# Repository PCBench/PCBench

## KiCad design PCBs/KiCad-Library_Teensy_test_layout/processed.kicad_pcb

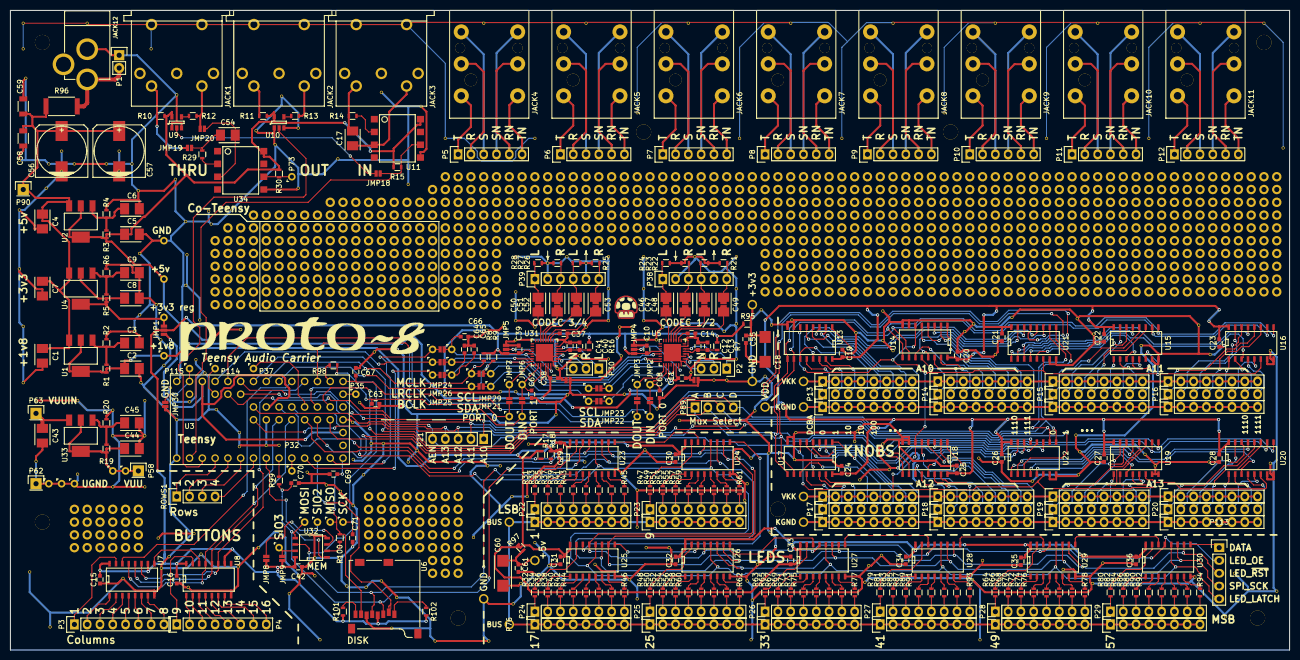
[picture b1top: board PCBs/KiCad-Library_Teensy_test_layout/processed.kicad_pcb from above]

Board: 2 copper layers, 254.0 x 127.0 mm, 372 parts (0 on the bottom side), 408 nets.

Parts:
C1, C2, C3, C4, C5, C6, C7, C8, C9, C43, C44, C45: 10u; TantalC_SizeB_EIA-3528_Reflow
C10, C11, C12, C13, C14, C37, C38, C39, C40, C41: 0.1uF; C_0603
C15, C16, C29, C30, C31, C32, C33, C34, C35, C36, C42: C; C_0603
C17, C54: D; TantalC_SizeB_EIA-3528_Reflow
C18, C60: 68uF; TantalC_SizeC_EIA-6032_Reflow
C19, C20, C21, C22, C23, C24, C25, C26, C27, C28: 1u; C_0603
C46, C47, C48, C49, C50, C51, C52, C53: 2.2u; TantalC_SizeB_EIA-3528_Reflow
C55, C61: 1uF; C_0603
C56, C57: 100u; c_elec_10x10.5
C58, C59: 1u; C_1206
C62, C63, C64, C65, C66, C67, C68, C69, C70, C71: 22p; C_0603
H1, H2, H3, H4, H5, H6, H7, H8: Hole; MountingHole_3mm
JACK1, JACK2, JACK3: DIN-5; SF-DIN-5
JACK4, JACK5, JACK6, JACK7, JACK8, JACK9, JACK10, JACK11: TRS_6term; SF-Neutrik-Jack-6-term
JACK12: POWER_JACKPTH; SparkFun-Connectors-POWER_JACK_PTH
JMP1, JMP4, JMP5: 3Jumper; SF-3way-open
JMP2, JMP3, JMP6, JMP7, JMP8, JMP9, JMP10, JMP11, JMP12, JMP13, JMP14, JMP15, JMP16, JMP17, JMP21, JMP22, JMP23, JMP24, JMP25, JMP26, JMP27, JMP28, JMP29, JMP30: 2Jumper; SF-2way-open
JMP18: THRU; SF-2way-open
JMP19, JMP20: IN2; SF-2way-open
P1: CONN_01X02; Pin_Header_Straight_1x02
P2, P30: CONN_01X03; Pin_Header_Straight_1x03
P3: COLS0; Pin_Header_Straight_1x08
P4: COLS1; Pin_Header_Straight_1x08
P5, P6, P7, P8, P9, P10, P11, P12, P38, P39: CONN_01X06; Pin_Header_Straight_1x06
P13, P14, P15, P16, P17, P18, P19, P20, P22, P23, P24, P25, P26, P27, P28, P29, P40, P41, P42, P43, P44, P45, P46, P47, P48, P49, P50, P51, P52, P53, P54, P55, P74, P75, P76, P77, P78, P79, P80, P81: CONN_01X08; Pin_Header_Straight_1x08
P21, P113: CONN_01X05; Pin_Header_Straight_1x05
P31, P36, P56, P57, P59, P60, P61, P104, P105, P114, P115: CONN_01X01; TestHole
P32: PIN8; TestHole
P33: SIO2; TestHole
P34: ~HOLD~/SIO3; TestHole
P35: PIN37; TestHole
P37: PIN31; TestHole
P58: VUU; Pin_Header_Straight_1x01
P62: UGND; Pin_Header_Straight_1x01
P63, P90: CONN_01X01; Pin_Header_Straight_1x01
P64: DIN1; TestHole
P65: DOUT1; TestHole
P66: SDA0_ISO; TestHole
P67: SCL0_ISO; TestHole
P68: MCLK_ISO; TestHole
P69: BCLK_ISO; TestHole
P70: LRCLK_ISO; TestHole
P71: DIN0; TestHole
P72: DOUT0; TestHole
P73: IN2TTL; TestHole
P82, P83, P84, P85, P86, P87, P88, P103, P106, P107, P108: CONN_01X01; PTH_LUG_.05
P89: CONN_01X04; Pin_Header_Straight_1x04
P91: SDA0; TestHole
P92: SCL0; TestHole
P93: MCLK; TestHole
P94: BCLK; TestHole
P95: LRCLK; TestHole
P96: DIN1_ISO; TestHole
P97: DOUT1_ISO; TestHole
P98: DIN0_ISO; TestHole
P99: DOUT0_ISO; TestHole
P100: SPI_MOSI; TestHole
P101: SPI_MISO; TestHole
P102: SPI_SCK; TestHole
P109: SCL_ISO; TestHole
P110: SDA_ISO; TestHole
P111: SCL_ISO2; TestHole
P112: SDA_ISO2; TestHole
R1, R3, R19: 11.3K; R_0603
R2, R4, R20: 34K; R_0603
R5: 11.5K; R_0603
R6: 18.7K; R_0603
R7, R16, R95, R97: 1; R_0603
R8, R9: 2.2K; R_0603
R10, R11, R12, R13, R14, R15, R29, R30: 220; R_0603
R17, R18, R101, R102: 4.7k; R_0603
R21, R22, R23, R24, R25, R26, R27, R28: 100k; R_0603
R31, R32, R33, R34, R35, R36, R37, R38, R39, R40, R41, R42, R43, R44, R45, R46, R47, R48, R49, R50, R51, R52, R53, R54, R55, R56, R57, R58, R59, R60, R61, R62, R63, R64, R65, R66, R67, R68, R69, R70, R71, R72, R73, R74, R75, R76, R77, R78, R79, R80, R81, R82, R83, R84, R85, R86, R87, R88, R89, R90, R91, R92, R93, R94: 470; R_0603
R96: 1; R_2512
R98, R99, R100: 50; R_0603
ROWS1: CONN_01X04; Pin_Header_Straight_1x04
U1, U2, U4, U33: LDO-adj-4term; SF-SOT-223
U3: Teensy_3.2; Teensy_3.2_Grid
U5, U31: SGTL5000; SF-QFN-32-NXP-SGTL5000
U6: SF-MicroSD-12term; SF-MICRO-SD
U7, U8, U23, U24, U25, U26, U27, U28, U29, U30: SF-74HC595; SF-SOIC-16
U9, U10: SF-74x125; SF-SOT-23-5
U11, U34: 2N168; SF-SMD-8
U13, U14, U15, U16, U17, U18, U19, U20, U21, U22: SF-4052; SF-SOIC-16
U32: SPI_MEMORY_SOIC8; SF-SOIC-8

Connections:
1/2AINL: C46.2, JMP13.1, U5.14
1/2AINR: C47.2, JMP12.1, U5.13
1/2AOUTL: C48.2, JMP11.1, U5.12
1/2AOUTR: C49.2, JMP10.1, U5.11
3/4AINL: C50.2, JMP17.1, U31.14
3/4AINR: C51.2, JMP16.1, U31.13
3/4AOUTL: C52.2, JMP15.1, U31.12
3/4AOUTR: C53.2, JMP14.1, U31.11
!LED_RST: P113.3, R18.1, U3.26, U23.10, U24.10, U25.10, U26.10, U27.10, U28.10, U29.10, U30.10
+1V8: C2.1, C11.1, C38.1, P104.1, R1.1, U1.2, U1.4, U5.30, U31.30
+3V3: C10.1, C15.1, C16.1, C39.1, C42.1, JMP1.2, JMP4.3, JMP5.3, JMP8.1, JMP9.1, R7.1, R8.1, R9.1, R16.1, R95.2, R101.1, R102.1, U5.20, U6.4, U7.10, U7.16, U8.10, U8.16, U31.20, U32.8
+3V3_REG: C8.1, JMP1.3, P105.1, R5.1, U4.2, U4.4
+3V3_TOUT: JMP1.1, U3.36, U3.40, U3.43
+5V: C5.1, C29.1, C30.1, C31.1, C32.1, C33.1, C34.1, C35.1, C36.1, P31.1, R3.1, R10.1, R11.1, R15.1, R17.1, R30.1, R97.2, U2.2, U2.4, U3.34, U9.5, U10.5, U11.8, U23.16, U24.16, U25.16, U26.16, U27.16, U28.16, U29.16, U30.16, U34.8
A: P89.1, U3.27, U13.10, U14.10, U15.10, U16.10, U17.10, U18.10, U19.10, U20.10
AGND: JMP30.2, P115.1, U3.35
AREF: P114.1, U3.48
B: P89.2, U3.28, U13.9, U14.9, U15.9, U16.9, U17.9, U18.9, U19.9, U20.9
BCLK: U3.16, U7.11, U8.11
BCLK_ISO: C65.1, JMP25.2, P69.1, U5.24, U31.24
BLATCH: U3.24, U7.12, U8.12
BOE: U3.25, U7.13, U8.13
BSER: U3.17, U7.14
C: P89.3, U3.29, U21.10, U22.10
CHASSIS: JACK1.6, JACK1.7, JACK2.6, JACK2.7, JACK3.6, JACK3.7
D: P89.4, U3.20, U21.9, U22.9
EN: P21.5, U3.21, U13.6, U14.6, U15.6, U16.6, U17.6, U18.6, U19.6, U20.6, U21.6, U22.6
GND: C1.2, C2.2, C3.2, C4.2, C5.2, C6.2, C7.2, C8.2, C9.2, C15.2, C16.2, C18.2, C19.2, C20.2, C21.2, C22.2, C23.2, C24.2, C25.2, C26.2, C27.2, C28.2, C29.2, C30.2, C31.2, C32.2, C33.2, C34.2, C35.2, C36.2, C42.2, C55.2, C56.2, C57.2, C58.2, C59.2, C60.2, C61.2, C62.2, C63.2, C64.2, C65.2, C66.2, C67.2, C68.2, C69.2, C70.2, C71.2, JACK12.GND, JMP27.1, JMP28.1, JMP30.1, P1.1, P36.1, P84.1, P107.1, R2.2, R4.2, R6.2, R18.2, U3.39, U3.42, U3.50, U6.6, U7.8, U8.8, U9.1, U9.3, U10.1, U10.3, U11.5, U13.7, U13.8, U14.7, U14.8, U15.7, U15.8, U16.7, U16.8, U17.7, U17.8, U18.7, U18.8, U19.7, U19.8, U20.7, U20.8, U21.7, U21.8, U22.7, U22.8, U23.8, U24.8, U25.8, U26.8, U27.8, U28.8, U29.8, U30.8, U32.4, U34.5
I2S_BCLK: JMP25.1, P94.1, U3.9
I2S_DIN0: JMP2.1, P71.1, U3.22
I2S_DIN0_ISO: C68.1, JMP2.2, P98.1, U5.26
I2S_DIN1: JMP6.1, P64.1, U3.15
I2S_DIN1_ISO: C62.1, JMP6.2, P96.1, U31.26
I2S_DOUT0: C67.1, JMP3.1, P72.1, U3.13
I2S_DOUT0_ISO: JMP3.2, P99.1, U5.25
I2S_DOUT1: C63.1, JMP7.1, P65.1, U3.30
I2S_DOUT1_ISO: JMP7.2, P97.1, U31.25
I2S_LRCLK: JMP26.1, P95.1, U3.23
I2S_MCLK: JMP24.1, P93.1, U3.11
ISOGND12: C10.2, C11.2, C12.2, C13.2, C14.2, JMP4.1, JMP27.2, P38.2, P38.5, R21.2, R22.2, R23.2, R24.2, U5.1, U5.3, U5.7, U5.32, U5.33
ISOGND34: C37.2, C38.2, C39.2, C40.2, C41.2, JMP5.1, JMP28.2, P39.2, P39.5, R25.2, R26.2, R27.2, R28.2, U31.1, U31.3, U31.7, U31.32, U31.33
K1: P13.1, U13.12
K2: P13.2, U13.14
K3: P13.3, U13.15
K4: P13.4, U13.11
K5: P13.5, U13.1
K6: P13.6, U13.5
K7: P13.7, U13.2
K8: P13.8, U13.4
K9: P14.1, U14.12
K10: P14.2, U14.14
K11: P14.3, U14.15
K12: P14.4, U14.11
K13: P14.5, U14.1
K14: P14.6, U14.5
K15: P14.7, U14.2
K16: P14.8, U14.4
K17: P15.1, U15.12
K18: P15.2, U15.14
K19: P15.3, U15.15
K20: P15.4, U15.11
K21: P15.5, U15.1
K22: P15.6, U15.5
K23: P15.7, U15.2
K24: P15.8, U15.4
K25: P16.1, U16.12
K26: P16.2, U16.14
K27: P16.3, U16.15
K28: P16.4, U16.11
K29: P16.5, U16.1
K30: P16.6, U16.5
K31: P16.7, U16.2
K32: P16.8, U16.4
K33: P17.1, U17.12
K34: P17.2, U17.14
K35: P17.3, U17.15
K36: P17.4, U17.11
K37: P17.5, U17.1
K38: P17.6, U17.5
K39: P17.7, U17.2
K40: P17.8, U17.4
K41: P18.1, U18.12
K42: P18.2, U18.14
K43: P18.3, U18.15
K44: P18.4, U18.11
K45: P18.5, U18.1
K46: P18.6, U18.5
K47: P18.7, U18.2
K48: P18.8, U18.4
K49: P19.1, U19.12
K50: P19.2, U19.14
K51: P19.3, U19.15
K52: P19.4, U19.11
K53: P19.5, U19.1
K54: P19.6, U19.5
K55: P19.7, U19.2
K56: P19.8, U19.4
K57: P20.1, U20.12
K58: P20.2, U20.14
K59: P20.3, U20.15
K60: P20.4, U20.11
K61: P20.5, U20.1
K62: P20.6, U20.5
K63: P20.7, U20.2
K64: P20.8, U20.4
KA0: P21.1, U3.44, U21.13
KA1: P21.2, U3.45, U21.3
KA2: P21.3, U3.46, U22.13
KA3: P21.4, U3.47, U22.3
KGND: P48.1, P48.2, P48.3, P48.4, P48.5, P48.6, P48.7, P48.8, P49.1, P49.2, P49.3, P49.4, P49.5, P49.6, P49.7, P49.8, P50.1, P50.2, P50.3, P50.4, P50.5, P50.6, P50.7, P50.8, P51.1, P51.2, P51.3, P51.4, P51.5, P51.6, P51.7, P51.8, P85.1
KGND2: P52.1, P52.2, P52.3, P52.4, P52.5, P52.6, P52.7, P52.8, P53.1, P53.2, P53.3, P53.4, P53.5, P53.6, P53.7, P53.8, P54.1, P54.2, P54.3, P54.4, P54.5, P54.6, P54.7, P54.8, P55.1, P55.2, P55.3, P55.4, P55.5, P55.6, P55.7, P55.8, P86.1
KOUT1: U13.13, U21.12
KOUT2: U13.3, U21.14
KOUT3: U14.13, U21.15
KOUT4: U14.3, U21.11
KOUT5: U15.13, U21.1
KOUT6: U15.3, U21.5
KOUT7: U16.13, U21.2
KOUT8: U16.3, U21.4
KOUT9: U17.13, U22.12
KOUT10: U17.3, U22.14
KOUT11: U18.13, U22.15
KOUT12: U18.3, U22.11
KOUT13: U19.13, U22.1
KOUT14: U19.3, U22.5
KOUT15: U20.13, U22.2
KOUT16: U20.3, U22.4
LED_BUS: P74.1, P74.2, P74.3, P74.4, P74.5, P74.6, P74.7, P74.8, P75.1, P75.2, P75.3, P75.4, P75.5, P75.6, P75.7, P75.8, P76.1, P76.2, P76.3, P76.4, P76.5, P76.6, P76.7, P76.8, P77.1, P77.2, P77.3, P77.4, P77.5, P77.6, P77.7, P77.8, P78.1, P78.2, P78.3, P78.4, P78.5, P78.6, P78.7, P78.8, P79.1, P79.2, P79.3, P79.4, P79.5, P79.6, P79.7, P79.8, P80.1, P80.2, P80.3, P80.4, P80.5, P80.6, P80.7, P80.8, P81.1, P81.2, P81.3, P81.4, P81.5, P81.6, P81.7, P81.8, P87.1, P88.1
LED_LATCH: P113.5, U3.32, U23.12, U24.12, U25.12, U26.12, U27.12, U28.12, U29.12, U30.12
LED_OE: P113.2, R17.2, U3.33, U23.13, U24.13, U25.13, U26.13, U27.13, U28.13, U29.13, U30.13
LRCLK_ISO: C64.1, JMP26.2, P70.1, U5.23, U31.23
MCLK_ISO: C66.1, JMP24.2, P68.1, U5.21, U31.21
unnamed: C3.1, R1.2, R2.1, U1.1
unnamed: C6.1, R3.2, R4.1, U2.1
unnamed: C9.1, R5.2, R6.1, U4.1
unnamed: C12.1, C13.1, R7.2, U5.5
unnamed: C14.1, U5.10
unnamed: C17.1, JACK3.5, U11.3
unnamed: C17.2, JACK3.4, R14.1
unnamed: C18.1, C55.1, P103.1, R95.1
unnamed: C37.1, U31.10
unnamed: C40.1, C41.1, R16.2, U31.5
unnamed: C45.1, R19.2, R20.1, U33.1
unnamed: C46.1, JMP13.2, P38.1, R24.1
unnamed: C47.1, JMP12.2, P38.3, R23.1
unnamed: C48.1, JMP11.2, P38.4, R22.1
unnamed: C49.1, JMP10.2, P38.6, R21.1
unnamed: C50.1, JMP17.2, P39.1, R28.1
unnamed: C51.1, JMP16.2, P39.3, R27.1
unnamed: C52.1, JMP15.2, P39.4, R26.1
unnamed: C53.1, JMP14.2, P39.6, R25.1
unnamed: C54.1, JMP20.1, U34.3
unnamed: C54.2, JMP19.1, R29.2
unnamed: C60.1, C61.1, P106.1, R97.1
unnamed: JACK1.4, JMP19.2, R10.2
unnamed: JACK1.5, JMP20.2, R12.1
unnamed: JACK2.4, R11.2
unnamed: JACK2.5, R13.1
unnamed: JACK4.G, P5.4
unnamed: JACK4.R, P5.2
unnamed: JACK4.RN, P5.5
unnamed: JACK4.S, P5.3
unnamed: JACK4.T, P5.1
unnamed: JACK4.TN, P5.6
unnamed: JACK5.G, P6.4
unnamed: JACK5.R, P6.2
unnamed: JACK5.RN, P6.5
unnamed: JACK5.S, P6.3
unnamed: JACK5.T, P6.1
unnamed: JACK5.TN, P6.6
unnamed: JACK6.G, P7.4
unnamed: JACK6.R, P7.2
unnamed: JACK6.RN, P7.5
unnamed: JACK6.S, P7.3
unnamed: JACK6.T, P7.1
unnamed: JACK6.TN, P7.6
unnamed: JACK7.G, P8.4
unnamed: JACK7.R, P8.2
unnamed: JACK7.RN, P8.5
unnamed: JACK7.S, P8.3
unnamed: JACK7.T, P8.1
unnamed: JACK7.TN, P8.6
unnamed: JACK8.G, P9.4
unnamed: JACK8.R, P9.2
unnamed: JACK8.RN, P9.5
unnamed: JACK8.S, P9.3
unnamed: JACK8.T, P9.1
unnamed: JACK8.TN, P9.6
unnamed: JACK9.G, P10.4
unnamed: JACK9.R, P10.2
unnamed: JACK9.RN, P10.5
unnamed: JACK9.S, P10.3
unnamed: JACK9.T, P10.1
unnamed: JACK9.TN, P10.6
unnamed: JACK10.G, P11.4
unnamed: JACK10.R, P11.2
unnamed: JACK10.RN, P11.5
unnamed: JACK10.S, P11.3
unnamed: JACK10.T, P11.1
unnamed: JACK10.TN, P11.6
unnamed: JACK11.G, P12.4
unnamed: JACK11.R, P12.2
unnamed: JACK11.RN, P12.5
unnamed: JACK11.S, P12.3
unnamed: JACK11.T, P12.1
unnamed: JACK11.TN, P12.6
unnamed: JMP4.2, U5.31
unnamed: JMP5.2, U31.31
unnamed: JMP8.2, P33.1, U32.3
unnamed: JMP9.2, P34.1, U32.7
unnamed: JMP18.2, U9.2
unnamed: P2.1, U5.6
unnamed: P2.2, U5.2
unnamed: P2.3, U5.4
unnamed: P3.1, U7.15
unnamed: P3.2, U7.1
unnamed: P3.3, U7.2
unnamed: P3.4, U7.3
unnamed: P3.5, U7.4
unnamed: P3.6, U7.5
unnamed: P3.7, U7.6
unnamed: P3.8, U7.7
unnamed: P4.1, U8.15
unnamed: P4.2, U8.1
unnamed: P4.3, U8.2
unnamed: P4.4, U8.3
unnamed: P4.5, U8.4
unnamed: P4.6, U8.5
unnamed: P4.7, U8.6
unnamed: P4.8, U8.7
unnamed: P22.1, R31.1
unnamed: P22.2, R33.1
unnamed: P22.3, R35.1
unnamed: P22.4, R37.1
unnamed: P22.5, R39.1
unnamed: P22.6, R41.1
unnamed: P22.7, R43.1
unnamed: P22.8, R45.1
unnamed: P23.1, R47.1
unnamed: P23.2, R49.1
unnamed: P23.3, R51.1
unnamed: P23.4, R53.1
unnamed: P23.5, R55.1
unnamed: P23.6, R57.1
unnamed: P23.7, R59.1
unnamed: P23.8, R61.1
unnamed: P24.1, R32.1
unnamed: P24.2, R34.1
unnamed: P24.3, R36.1
unnamed: P24.4, R38.1
unnamed: P24.5, R40.1
unnamed: P24.6, R42.1
unnamed: P24.7, R44.1
unnamed: P24.8, R46.1
unnamed: P25.1, R48.1
unnamed: P25.2, R50.1
unnamed: P25.3, R52.1
unnamed: P25.4, R54.1
unnamed: P25.5, R56.1
unnamed: P25.6, R58.1
unnamed: P25.7, R60.1
unnamed: P25.8, R62.1
unnamed: P26.1, R63.1
unnamed: P26.2, R65.1
unnamed: P26.3, R67.1
unnamed: P26.4, R69.1
unnamed: P26.5, R71.1
unnamed: P26.6, R73.1
unnamed: P26.7, R75.1
unnamed: P26.8, R77.1
unnamed: P27.1, R79.1
unnamed: P27.2, R81.1
unnamed: P27.3, R83.1
unnamed: P27.4, R85.1
unnamed: P27.5, R87.1
unnamed: P27.6, R89.1
unnamed: P27.7, R91.1
unnamed: P27.8, R93.1
unnamed: P28.1, R64.1
unnamed: P28.2, R66.1
unnamed: P28.3, R68.1
unnamed: P28.4, R70.1
unnamed: P28.5, R72.1
unnamed: P28.6, R74.1
unnamed: P28.7, R76.1
unnamed: P28.8, R78.1
unnamed: P29.1, R80.1
unnamed: P29.2, R82.1
unnamed: P29.3, R84.1
unnamed: P29.4, R86.1
unnamed: P29.5, R88.1
unnamed: P29.6, R90.1
unnamed: P29.7, R92.1
unnamed: P29.8, R94.1
unnamed: P30.1, U31.6
unnamed: P30.2, U31.2
unnamed: P30.3, U31.4
unnamed: P32.1, U3.8
unnamed: P35.1, U3.37
unnamed: P37.1, U3.31
unnamed: P73.1, R30.2, U34.6
unnamed: P113.1, U30.9
unnamed: R12.2, U9.4
unnamed: R13.2, U10.4
unnamed: R14.2, U11.2
unnamed: R29.1, U34.2
unnamed: R31.2, U23.15
unnamed: R32.2, U25.15
unnamed: R33.2, U23.1
unnamed: R34.2, U25.1
unnamed: R35.2, U23.2
unnamed: R36.2, U25.2
unnamed: R37.2, U23.3
unnamed: R38.2, U25.3
unnamed: R39.2, U23.4
unnamed: R40.2, U25.4
unnamed: R41.2, U23.5
unnamed: R42.2, U25.5
unnamed: R43.2, U23.6
unnamed: R44.2, U25.6
unnamed: R45.2, U23.7
unnamed: R46.2, U25.7
unnamed: R47.2, U24.15
unnamed: R48.2, U26.15
unnamed: R49.2, U24.1
unnamed: R50.2, U26.1
unnamed: R51.2, U24.2
unnamed: R52.2, U26.2
unnamed: R53.2, U24.3
unnamed: R54.2, U26.3
unnamed: R55.2, U24.4
unnamed: R56.2, U26.4
unnamed: R57.2, U24.5
unnamed: R58.2, U26.5
unnamed: R59.2, U24.6
unnamed: R60.2, U26.6
unnamed: R61.2, U24.7
unnamed: R62.2, U26.7
unnamed: R63.2, U27.15
unnamed: R64.2, U29.15
unnamed: R65.2, U27.1
unnamed: R66.2, U29.1
unnamed: R67.2, U27.2
unnamed: R68.2, U29.2
unnamed: R69.2, U27.3
unnamed: R70.2, U29.3
unnamed: R71.2, U27.4
unnamed: R72.2, U29.4
unnamed: R73.2, U27.5
unnamed: R74.2, U29.5
unnamed: R75.2, U27.6
unnamed: R76.2, U29.6
unnamed: R77.2, U27.7
unnamed: R78.2, U29.7
unnamed: R79.2, U28.15
unnamed: R80.2, U30.15
unnamed: R81.2, U28.1
unnamed: R82.2, U30.1
unnamed: R83.2, U28.2
unnamed: R84.2, U30.2
unnamed: R85.2, U28.3
unnamed: R86.2, U30.3
unnamed: R87.2, U28.4
unnamed: R88.2, U30.4
unnamed: R89.2, U28.5
unnamed: R90.2, U30.5
unnamed: R91.2, U28.6
unnamed: R92.2, U30.6
unnamed: R93.2, U28.7
unnamed: R94.2, U30.7
unnamed: R101.2, U6.8
unnamed: R102.2, U6.1
unnamed: U7.9, U8.14
unnamed: U23.9, U24.14
unnamed: U24.9, U25.14
unnamed: U25.9, U26.14
unnamed: U26.9, U27.14
unnamed: U27.9, U28.14
unnamed: U28.9, U29.14
unnamed: U29.9, U30.14
PORT-RX: JMP18.1, R15.2, U3.0, U11.6
PORT-TX: U3.1, U10.2
PWR: JACK12.PWR, P1.2, R96.2
RAM_CS: U3.6, U32.1
ROW1: ROWS1.1, U3.2
ROW2: ROWS1.2, U3.3
ROW3: ROWS1.3, U3.4
ROW4: ROWS1.4, U3.5
SCL0: JMP29.1, P109.1, R8.2, U3.19
SCL12: JMP23.2, P67.1, U5.29
SCL34: JMP23.1, JMP29.2, P92.1, P111.1, U31.29
SDA0: JMP21.1, P110.1, R9.2, U3.18
SDA12: JMP22.2, P66.1, U5.27
SDA34: JMP21.2, JMP22.1, P91.1, P112.1, U31.27
SD_CS: U3.10, U6.2
SPI_MISO: C69.1, P101.1, R100.2, U3.12, U6.7
SPI_MISO_SRC: R100.1, U32.2
SPI_MOSI: C70.1, P100.1, R99.2, U6.3, U23.14, U32.5
SPI_MOSI_SRC: R99.1, U3.7
SPI_SCK: C71.1, P102.1, P113.4, R98.2, U6.5, U23.11, U24.11, U25.11, U26.11, U27.11, U28.11, U29.11, U30.11, U32.6
SPI_SCK_SRC: R98.1, U3.14
UGND: C43.2, C44.2, C45.2, P59.1, P60.1, P61.1, P62.1, R20.2
VBULK: C1.1, C4.1, C7.1, C56.1, C57.1, C58.1, C59.1, P90.1, R96.1, U1.3, U2.3, U4.3
VDD: C19.1, C20.1, C21.1, C22.1, C23.1, C24.1, C25.1, C26.1, C27.1, C28.1, P108.1, U13.16, U14.16, U15.16, U16.16, U17.16, U18.16, U19.16, U20.16, U21.16, U22.16
VKK: P40.1, P40.2, P40.3, P40.4, P40.5, P40.6, P40.7, P40.8, P41.1, P41.2, P41.3, P41.4, P41.5, P41.6, P41.7, P41.8, P42.1, P42.2, P42.3, P42.4, P42.5, P42.6, P42.7, P42.8, P43.1, P43.2, P43.3, P43.4, P43.5, P43.6, P43.7, P43.8, P82.1
VKK2: P44.1, P44.2, P44.3, P44.4, P44.5, P44.6, P44.7, P44.8, P45.1, P45.2, P45.3, P45.4, P45.5, P45.6, P45.7, P45.8, P46.1, P46.2, P46.3, P46.4, P46.5, P46.6, P46.7, P46.8, P47.1, P47.2, P47.3, P47.4, P47.5, P47.6, P47.7, P47.8, P83.1
VUU: C44.1, P56.1, P57.1, P58.1, R19.1, U33.2, U33.4
VUUIN: C43.1, P63.1, U33.3

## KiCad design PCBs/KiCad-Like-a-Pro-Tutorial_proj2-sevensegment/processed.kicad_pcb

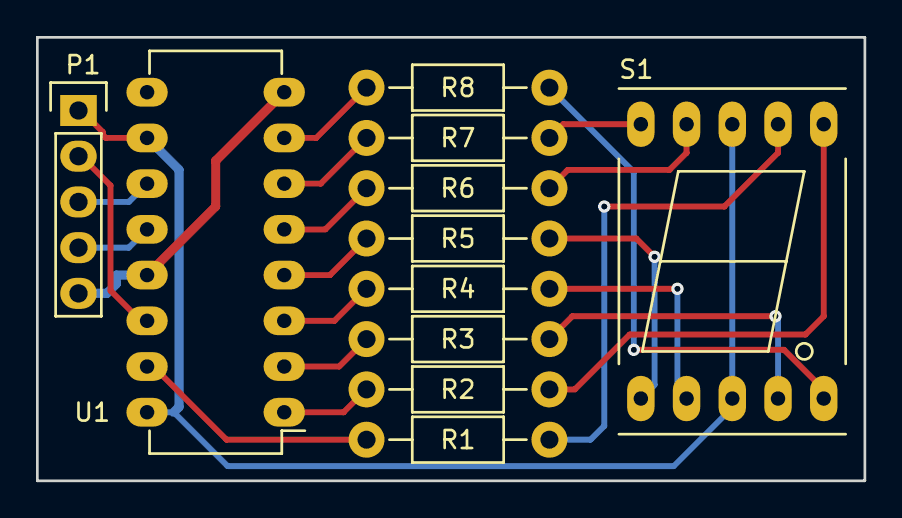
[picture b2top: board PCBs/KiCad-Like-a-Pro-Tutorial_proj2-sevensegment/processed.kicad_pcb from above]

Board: 2 copper layers, 46.0 x 24.6 mm, 11 parts (0 on the bottom side), 21 nets.

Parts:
P1: CONN_01X05; Pin_Header_Straight_1x05
R1, R2, R3, R4, R5, R6, R7, R8: 220; Resistor_Horizontal_RM10mm
S1: 7SEGM; 7SegmentLED_LTS6760_LTS6780
U1: 74HC595; DIP-16_W7.62mm_LongPads

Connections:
/A: R1.1, S1.7
/B: R2.1, S1.6
/C: R3.1, S1.4
/CLOCK: P1.4, U1.12
/D: R4.1, S1.2
/DATA: P1.3, U1.11
/E: R5.1, S1.1
/F: R6.1, S1.9
/G: R7.1, S1.10
/H: R8.1, S1.5
/LATCH: P1.2, U1.14
/QA: R1.2, U1.15
/QB: R2.2, U1.1
/QC: R3.2, U1.2
/QD: R4.2, U1.3
/QE: R5.2, U1.4
/QF: R6.2, U1.5
/QG: R7.2, U1.6
/QH: R8.2, U1.7
GND: P1.5, U1.8, U1.13
VCC: P1.1, S1.3, S1.8, U1.10, U1.16

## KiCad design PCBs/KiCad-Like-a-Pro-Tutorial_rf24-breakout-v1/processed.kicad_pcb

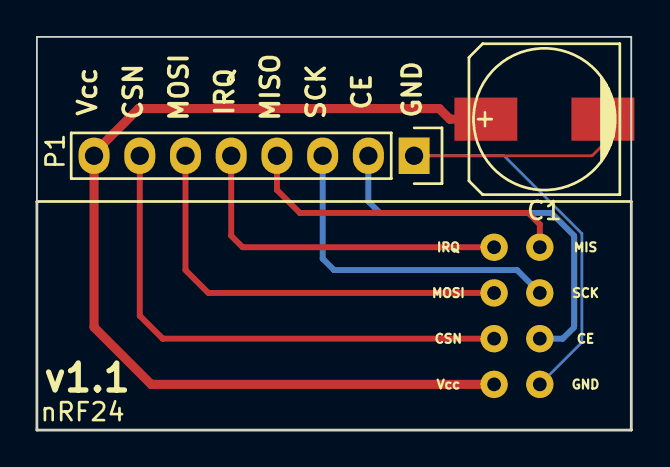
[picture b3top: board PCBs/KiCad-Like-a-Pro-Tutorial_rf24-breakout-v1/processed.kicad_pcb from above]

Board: 2 copper layers, 33.0 x 21.8 mm, 3 parts (0 on the bottom side), 8 nets.

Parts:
C1: 1uF; c_elec_8x10.5
P1: CONN_01X08; Pin_Header_Straight_1x08
U1: nRF24

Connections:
/CE: P1.2, U1.1
/CSN: P1.7, U1.6
/IRQ: P1.5, U1.4
/MIS: P1.4, U1.3
/MOSI: P1.6, U1.5
/SCK: P1.3, U1.2
/Vcc: C1.1, P1.8, U1.7
GND: C1.2, P1.1, U1.0

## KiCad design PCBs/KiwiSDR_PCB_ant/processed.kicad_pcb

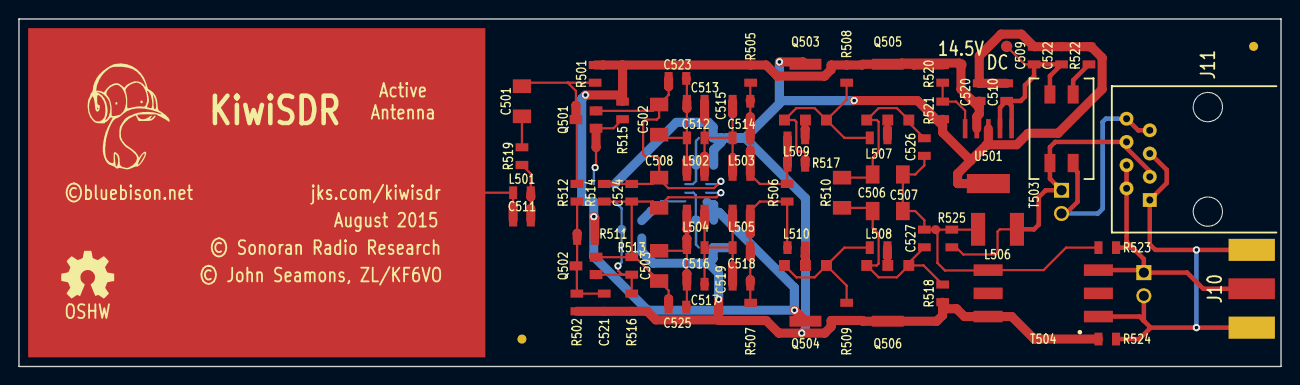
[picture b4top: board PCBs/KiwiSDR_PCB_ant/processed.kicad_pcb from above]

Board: 2 copper layers, 138.0 x 38.0 mm, 85 parts (0 on the bottom side), 36 nets.

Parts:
C501, C502, C503, C506, C507, C508: 470n/100; kiwi-SM1206
C504, C505: DNL 470n/100; kiwi-SM1206
C509: 100n/100; kiwi-SM0805
C510, C520: 10u/25; kiwi-SM0805
C511, C512, C513, C514, C515, C516, C517, C518, C519: DNL; kiwi-SM0805
C521: DNL 100n/100; kiwi-SM0805
C522, C523, C524, C525, C526, C527: 1n/100; kiwi-SM0805
EP501: E_FIELD_PROBE; kiwi-E_FIELD_PROBE
FID1, FID2: FIDUCIAL; kiwi-FIDUCIAL_2_SIDE
GFX1: LOGO; kiwi-KIWI_10MM
GFX3: OSHW; kiwi-OSHW_6MM
J10: DNL BNC; kiwi-BNC_SMA_NO_VIP
J11: DNL RJ45; kiwi-RJ45_8
J12: DNL TB_2; kiwi-TB_2P_2_54MM
J13: TB_2; kiwi-TB_2P_2_54MM
L501, L502, L503, L504, L505: 0R; kiwi-SM0805
L506: 100uH; kiwi-SM1812
L507, L508, L509, L510: FB 80Z; kiwi-SM0805
Q501: J310; kiwi-SOT23_DGS
Q502: J271; kiwi-SOT23_DGS
Q503, Q506: BFG31; kiwi-SOT223_EBEC
Q504, Q505: BFG35; kiwi-SOT223_EBEC
Q507: DNL J310; kiwi-SOT23_DGS
R501, R502: 1M; kiwi-SM0805
R503, R504: DNL 100R; kiwi-SM0805
R505, R507: 100K; kiwi-SM0805
R506: 2K2; kiwi-SM0805
R508, R509: 470R; kiwi-SM0805
R510: 10R/0.66W; kiwi-SM1206
R511: DNL 1M; kiwi-SM0805
R512, R515, R516, R519, R523, R524: 0R; kiwi-SM0805
R513, R518: DNL 0R; kiwi-SM0805
R514: 100R; kiwi-SM0805
R517: DNL 47R; kiwi-SM0805
R520: 11K; kiwi-SM0805
R521: 1K; kiwi-SM0805
R522: DNL; kiwi-SM0805
R525: 1K5; kiwi-SM0805
T501: DNL T-622; kiwi-MCL_KK81
T502, T504: DNL T1-6; kiwi-MCL_KK81
T503: CMC 2 mH; kiwi-CMC
TP501, TP502: TEST_POINT; kiwi-TP_1250
U501: TPS7A4501; kiwi-SOT223_6

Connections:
/14.55: C520.1, Q504.C, Q505.C, R501.1, R503.1, R505.1, R508.1, R511.1, R515.1, R520.1, T501.3, T502.4, TP502.1, U501.4
/ANT2: C511.2, L501.1, R519.1
/ANT3: C501.1, R519.2
/ANT4: C501.2, Q501.G, R501.2, R512.1
/B1H: L509.2, Q503.B
/B1L: L510.2, Q504.B
/B2H: L507.2, Q505.B
/B2L: L508.2, Q506.B
/BIAS: C521.1, Q502.G, R502.2, R511.2, R512.2
/BIAS+: J11.3, J11.6, J12.1, L506.2, R525.1, T503.3
/BIAS-: J11.7, J11.8, J12.2, T503.4
/DCIN: C509.1, C510.1, C522.1, T503.2, TP501.1, U501.1, U501.2
/E1H: L507.1, Q503.E1, Q503.E2, R508.2, R517.1
/E1L: L508.1, Q504.E1, Q504.E2, R509.1
/E2H: C506.1, C526.1, Q505.E1, Q505.E2, R510.1
/E2L: C507.1, C527.1, Q506.E1, Q506.E2, R510.2, R518.1
/EPROBE: C511.1, EP501.1, L501.2
/FB1: Q501.D, R515.2, T502.6
/FB2: Q502.D, Q507.G, R513.1, R516.2, T502.3
/FB3: Q507.D, T501.4
/JHI: C502.1, C508.1, C523.1, C524.1, Q501.S, R514.2, T501.1
/JLO: C503.1, C508.2, C524.2, C525.1, Q502.S, R513.2, R514.1, T501.2
/NF1H: C502.2, C512.1, C513.1, C523.2, L502.1
/NF1L: C503.2, C516.1, C517.1, C525.2, L504.1
/NF2H: C512.2, C513.2, C514.1, C515.1, L502.2, L503.1
/NF2L: C516.2, C517.2, C518.1, C519.1, L504.2, L505.1
/NF3H: C514.2, C515.2, L503.2, L509.1, R505.2, R506.1, R517.2
/NF3L: C518.2, C519.2, L505.2, L510.1, R506.2, R507.1
/OUT: C506.2, C507.2, C526.2, C527.2, L506.1, R523.2, R525.2, T504.3
/RX+: J10.1, J11.2, J11.4, J13.1, R523.1, T504.4
/RX-: J10.2, J10.3, J11.1, J11.5, J13.2, R524.1, T504.6
/THI: C505.1, R504.2, T501.6
/TLO: C504.2, R503.2, T501.5
/TP: R522.1, T503.1
/VADJ: R520.2, R521.2, U501.5
GND: C504.1, C505.2, C509.2, C510.2, C520.2, C521.2, C522.2, Q503.C, Q506.C, Q507.S, R502.1, R504.1, R507.2, R509.2, R516.1, R518.2, R521.1, R522.2, R524.2, T502.1, T504.1, U501.3, U501.TAB

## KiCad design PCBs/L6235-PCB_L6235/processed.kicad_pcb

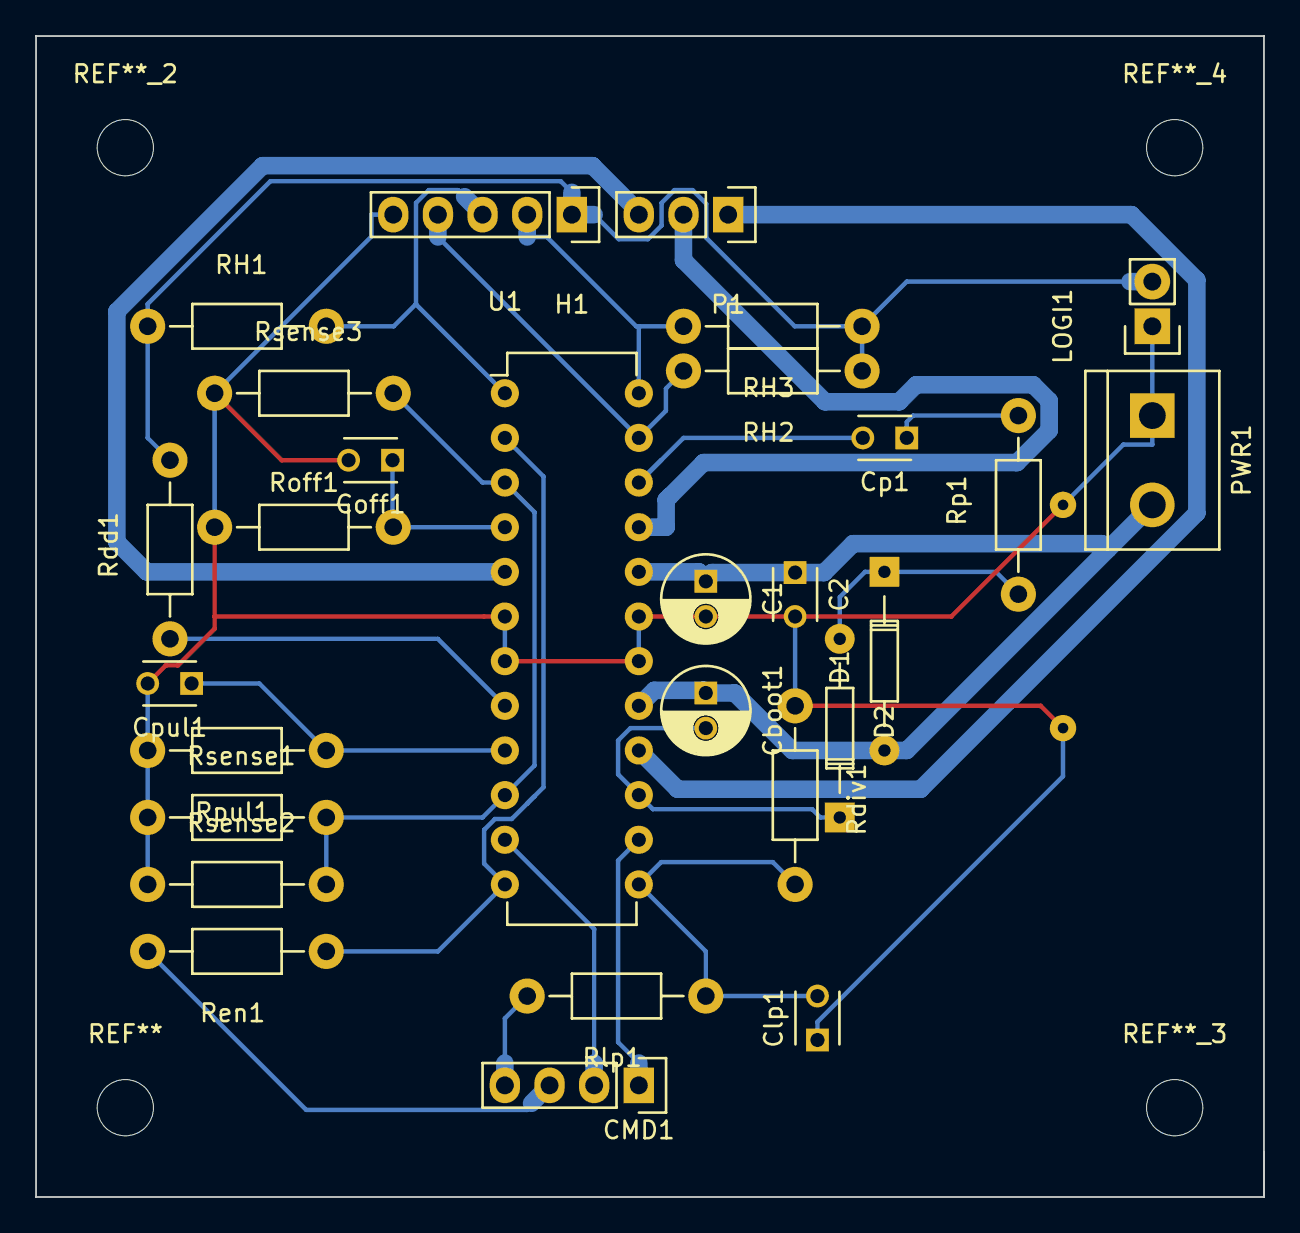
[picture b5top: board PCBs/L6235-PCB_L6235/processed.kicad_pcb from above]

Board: 2 copper layers, 69.8 x 66.0 mm, 30 parts (0 on the bottom side), 23 nets.

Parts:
C1: 10µ; C_Radial_D5_L11_P2
C2: 100n; C_Disc_D3_P2.5
CMD1: CONN_01X04; Socket_Strip_Straight_1x04
Cboot1: 220n; C_Radial_D5_L11_P2
Clp1: 100n; C_Disc_D3_P2.5
Coff1: 1n; C_Disc_D3_P2.5
Cp1: 10n; C_Disc_D3_P2.5
Cpul1: 10n; C_Disc_D3_P2.5
D1, D2: 1N4148; Diode_DO-35_SOD27_Horizontal_RM10
H1: CONN_01X05; Socket_Strip_Straight_1x05
LOGI1: CONN_01X02; Socket_Strip_Straight_1x02
Noname_1, Noname_2: pad_gnd
P1: CONN_01X03; Socket_Strip_Straight_1x03
PWR1: CONN_01X02; bornier2
RH1, RH2, RH3: 10K; Resistor_Horizontal_RM10mm
Rdd1: 1k; Resistor_Horizontal_RM10mm
Rdiv1: 15k; Resistor_Horizontal_RM10mm
Ren1: 100k; Resistor_Horizontal_RM10mm
Rlp1: 56k; Resistor_Horizontal_RM10mm
Roff1: 33k; Resistor_Horizontal_RM10mm
Rp1: 100; Resistor_Horizontal_RM10mm
Rpul1: 47k; Resistor_Horizontal_RM10mm
Rsense1, Rsense2, Rsense3: 1; Resistor_Horizontal_RM10mm
U1: L6235N; DIP-24_W7.62mm

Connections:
+5V: H1.1, LOGI1.2, RH1.1, RH2.1, RH3.1, Rdd1.2
/BRAKE: CMD1.1, U1.14
/ENABLE: CMD1.3, Ren1.2
/FWD/REV: CMD1.2, U1.11
/HALL1: H1.3, RH1.2, U1.1
/HALL2: H1.4, RH2.2, U1.23
/HALL3: H1.2, RH3.2, U1.24
/PHASE1: P1.3, U1.5
/PHASE2: P1.2, U1.21
/PHASE3: P1.1, U1.16
/VREF: CMD1.4, Rlp1.2
GND: C1.2, C2.2, Clp1.1, Coff1.2, Cpul1.2, H1.5, LOGI1.1, Noname_1.1, Noname_2.1, PWR1.1, Rdiv1.1, Roff1.2, Rpul1.2, Rsense1.1, Rsense2.1, Rsense3.1, U1.6, U1.7, U1.18, U1.19
unnamed: Cboot1.2, D2.1, U1.15
unnamed: Clp1.2, Rdiv1.2, Rlp1.1, U1.13
unnamed: Coff1.1, Roff1.1, U1.4
unnamed: Cp1.1, Rp1.2
unnamed: Cp1.2, U1.22
unnamed: Cpul1.1, Rpul1.1, U1.9
unnamed: D1.1, D2.2, Rp1.1
unnamed: Rdd1.1, U1.8
unnamed: Ren1.1, U1.2, U1.12
unnamed: Rsense1.2, Rsense2.2, Rsense3.2, U1.3, U1.10
VSS: C1.1, C2.1, Cboot1.1, D1.2, PWR1.2, U1.17, U1.20

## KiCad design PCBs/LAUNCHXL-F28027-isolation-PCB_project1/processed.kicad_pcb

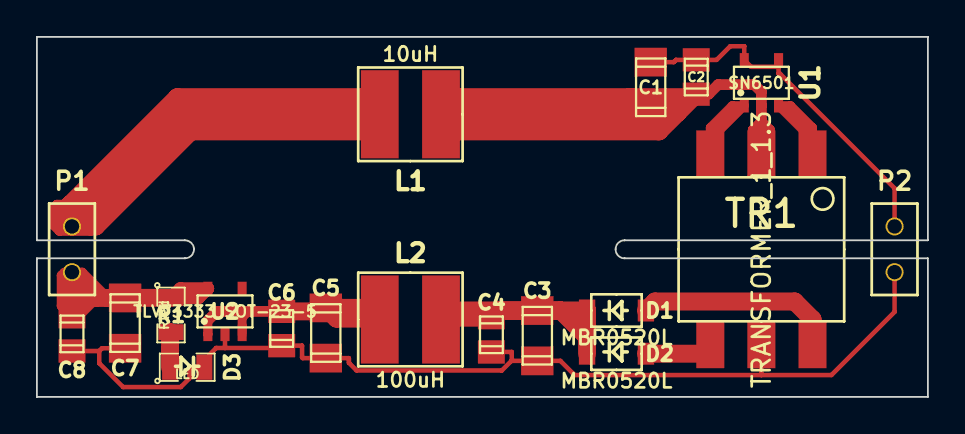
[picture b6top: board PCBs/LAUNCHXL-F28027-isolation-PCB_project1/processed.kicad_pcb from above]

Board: 2 copper layers, 49.5 x 20.0 mm, 19 parts (0 on the bottom side), 12 nets.

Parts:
C1, C3, C5, C7: 4.7u; c_1206
C2, C4, C6, C8: 100n; c_0805
D1, D2: MBR0520L; SOD-123
D3: LED; SM0805
L1: 10uH; VLCF5020
L2: 100uH; VLCF5020
P1, P2: CONN_2; PIN_ARRAY_2X1
R1: Rled; SM0805
TR1: TRANSFORMER_1_1.3; transf_isol_wurth
U1: SN6501; SOT23-5
U2: TLV73333 SOT-23-5; SOT23-5

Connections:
3.3V: L1.1, P1.2
3.3V isol: C7.1, C8.1, P1.1, R1.1, U2.5
GND: C1.2, C2.2, P2.2, U1.4, U1.5
GND_isol: C3.2, C4.2, C5.2, C6.2, C7.2, C8.2, D3.2, P2.1, TR1.5, U2.2
unnamed: C1.1, C2.1, L1.2, TR1.2, U1.2
unnamed: D3.1, R1.2
unnamed: TR1.1, U1.3
unnamed: TR1.3, U1.1
unnamed: C3.1, C4.1, D1.2, D2.2, L2.1
unnamed: D1.1, TR1.6
unnamed: D2.1, TR1.4
unnamed: C5.1, C6.1, L2.2, U2.1, U2.3

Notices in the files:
PCBs/KiwiSDR_PCB_ant/processed.kicad_pcb:
© John Seamons, ZL/KF6VO
© Sonoran Radio Research
©bluebison.net
